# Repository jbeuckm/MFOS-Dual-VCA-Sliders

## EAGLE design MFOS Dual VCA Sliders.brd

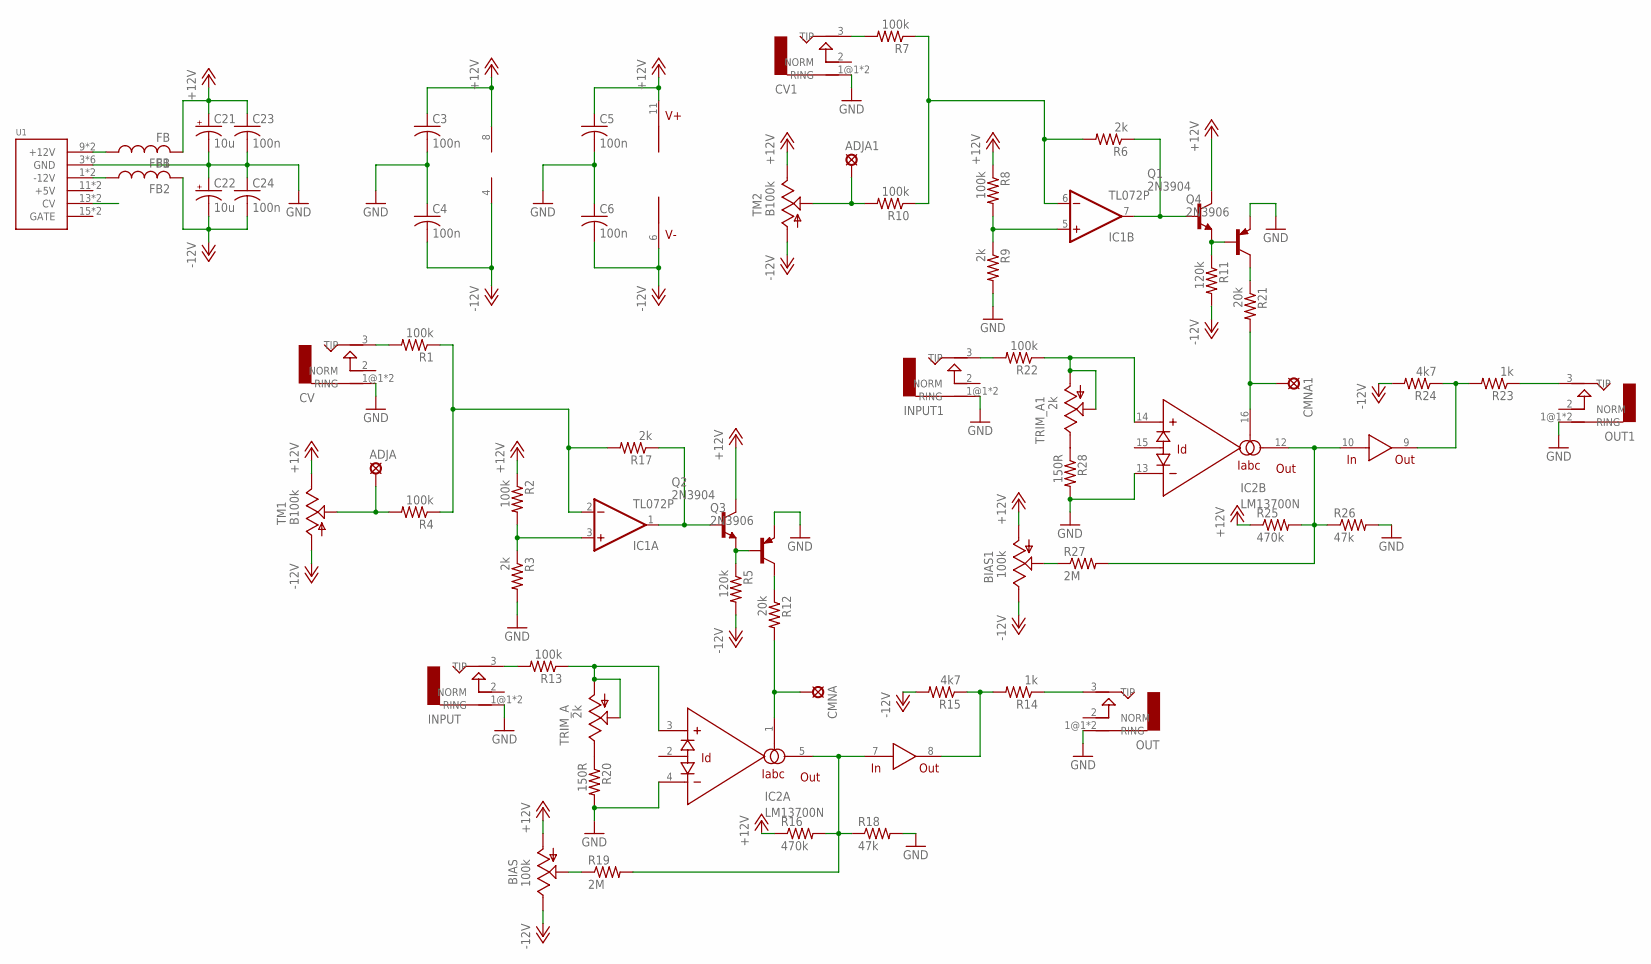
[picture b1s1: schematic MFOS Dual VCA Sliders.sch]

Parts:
ADJA, ADJA1: LSP10
BIAS, BIAS1: 100k; B64W
C3, C4, C5, C6: 100n; C1206
C21, C22: 10u; B45181A
C23, C24: 100n; C050-024X044
CMNA, CMNA1: LSP10
CV, CV1: AUDIO-JACKERTHENVAR; ERTHENVAR-JACK
FB1, FB2: FB
IC1: TL072P; DIL08
IC2: LM13700N; DIL16
INPUT, INPUT1: AUDIO-JACKERTHENVAR; ERTHENVAR-JACK
OUT, OUT1: AUDIO-JACKERTHENVAR; ERTHENVAR-JACK
Q1, Q2: 2N3904; TO92
Q3, Q4: 2N3906; TO92
R1, R2, R4, R7, R8, R10, R13, R22: 100k; R1206
R3, R6, R9, R17: 2k; R1206
R5, R11: 120k; R1206
R12, R21: 20k; R1206
R14, R23: 1k; R1206
R15, R24: 4k7; R1206
R16, R25: 470k; R1206
R18, R26: 47k; R1206
R19, R27: 2M; R1206
R20, R28: 150R; R1206
TM1, TM2: B100k; SLIDEPOT-60
TRIM_A, TRIM_A1: 2k; B64W
U1: POWER; POWER_16

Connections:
+12V: BIAS.A, BIAS1.A, C3.1, C5.1, C21.+, C23.1, FB1.P$2 (2), IC1.8 (V+), IC2.11 (V+), Q1.1 (C), Q2.1 (C), R2.1, R8.1, R16.1, R25.1, TM1.B, TM2.B
-12V: BIAS.E, BIAS1.E, C4.2, C6.2, C22.-, C24.2, FB2.P$2 (2), IC1.4 (V-), IC2.6 (V-), R5.2, R11.2, R15.2, R24.2, TM1.A, TM2.A
GND: C3.2, C4.1, C5.2, C6.1, C21.-, C22.+, C23.2, C24.1, CV.1@1 (RING), CV.1@2 (RING), CV1.1@1 (RING), CV1.1@2 (RING), IC2.4 (-IN), IC2.13 (-IN), INPUT.1@1 (RING), INPUT.1@2 (RING), INPUT1.1@1 (RING), INPUT1.1@2 (RING), OUT.1@1 (RING), OUT.1@2 (RING), OUT1.1@1 (RING), OUT1.1@2 (RING), Q3.3 (E), Q4.3 (E), R3.2, R9.2, R18.2, R20.2, R26.2, R28.2, U1.3 (GND), U1.4 (GND), U1.5 (GND), U1.6 (GND), U1.7 (GND), U1.8 (GND)
unnamed: IC1.7 (OUT), Q1.2 (B), R6.1
unnamed: IC1.5 (+IN), R8.2, R9.1
unnamed: CV.3 (TIP), R1.2
unnamed: CV1.3 (TIP), R7.2
unnamed: ADJA.MP, R4.2, TM1.WIPER
unnamed: IC1.2 (-IN), R1.1, R4.1, R17.2
unnamed: Q2.3 (E), Q3.2 (B), R5.1
unnamed: IC1.1 (OUT), Q2.2 (B), R17.1
unnamed: ADJA1.MP, R10.2, TM2.WIPER
unnamed: IC1.6 (-IN), R6.2, R7.1, R10.1
unnamed: IC1.3 (+IN), R2.2, R3.1
unnamed: Q3.1 (C), R12.1
unnamed: INPUT.3 (TIP), R13.2
unnamed: Q1.3 (E), Q4.2 (B), R11.1
unnamed: Q4.1 (C), R21.1
unnamed: CMNA.MP, IC2.1 (IABC), R12.2
unnamed: INPUT1.3 (TIP), R22.2
unnamed: BIAS.P$1 (S), BIAS.S, R19.1
unnamed: OUT.3 (TIP), R14.1
unnamed: IC2.8 (OUT), R14.2, R15.1
unnamed: IC2.5 (OUT), IC2.7 (IN), R16.2, R18.1, R19.2
unnamed: R20.1, TRIM_A.E
unnamed: IC2.3 (+IN), R13.1, TRIM_A.A, TRIM_A.P$1 (S), TRIM_A.S
unnamed: CMNA1.MP, IC2.16 (IABC), R21.2
unnamed: IC2.9 (OUT), R23.2, R24.1
unnamed: OUT1.3 (TIP), R23.1
unnamed: IC2.10 (IN), IC2.12 (OUT), R25.2, R26.1, R27.2
unnamed: BIAS1.P$1 (S), BIAS1.S, R27.1
unnamed: R28.1, TRIM_A1.E
unnamed: IC2.14 (+IN), R22.1, TRIM_A1.A, TRIM_A1.P$1 (S), TRIM_A1.S
unnamed: U1.13 (CV), U1.14 (CV)
unnamed: FB1.P$1 (1), U1.9 (+12V), U1.10 (+12V)
unnamed: FB2.P$1 (1), U1.1 (-12V), U1.2 (-12V)

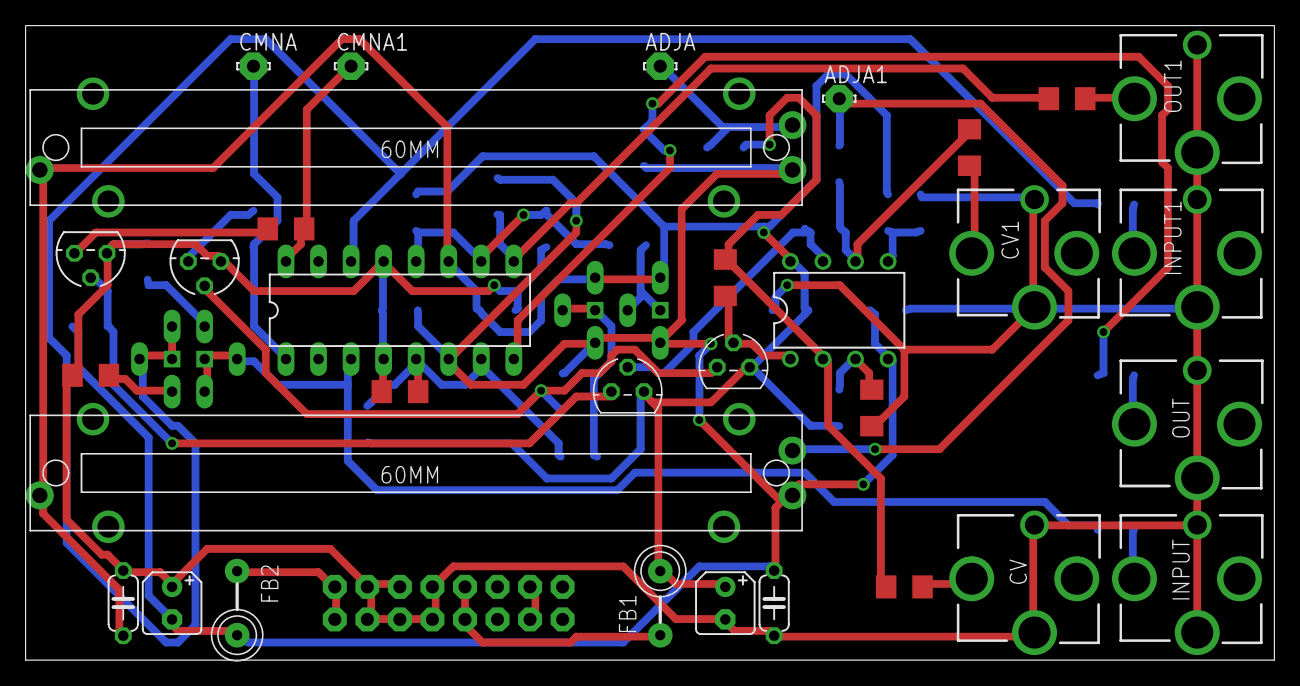
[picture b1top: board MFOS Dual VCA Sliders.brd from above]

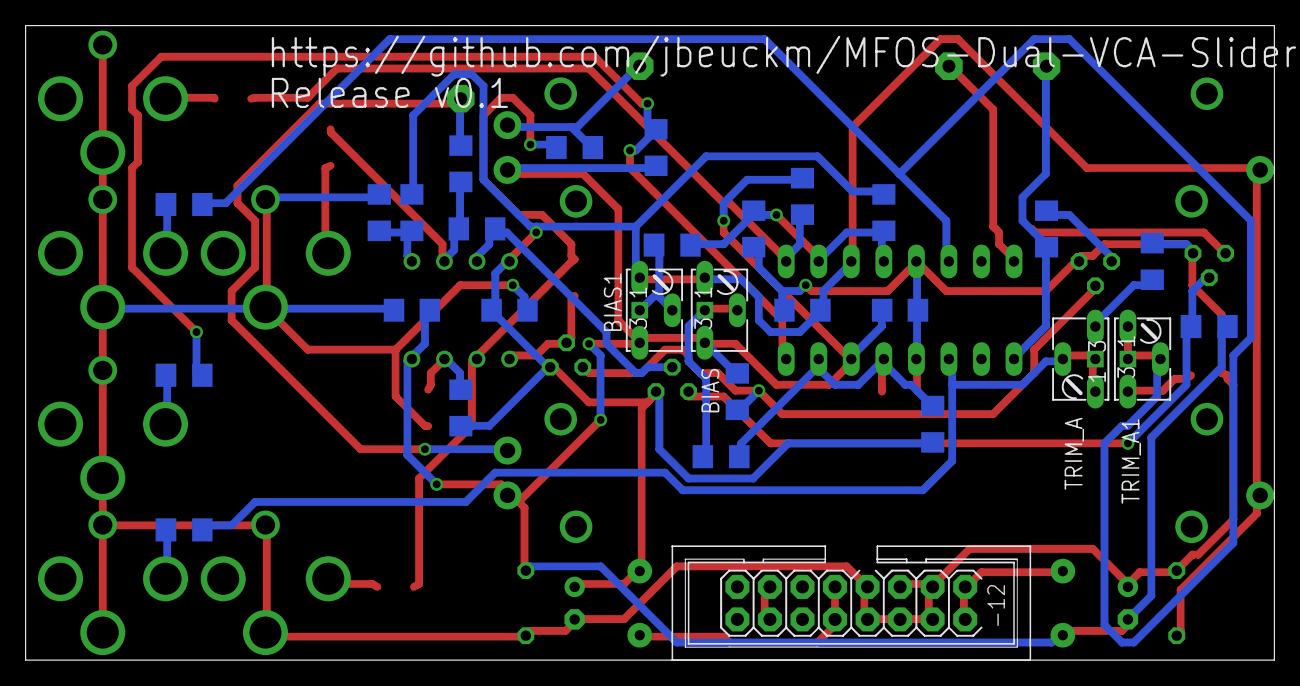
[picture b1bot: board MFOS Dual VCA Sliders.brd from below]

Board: 2 copper layers, 97.5 x 49.5 mm, 61 parts (29 on the bottom side), 36 nets.

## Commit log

2017-08-28 added copy on other half of 13700
2017-08-28 smt board begun
2017-08-28 routed with smt resistors
2017-08-28 moved labels into view
2017-08-29 url on board
2017-08-29 fixed a label
